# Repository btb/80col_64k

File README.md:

# 80col_64k

Clone of the Extended 80-Column Text Card for Apple IIe

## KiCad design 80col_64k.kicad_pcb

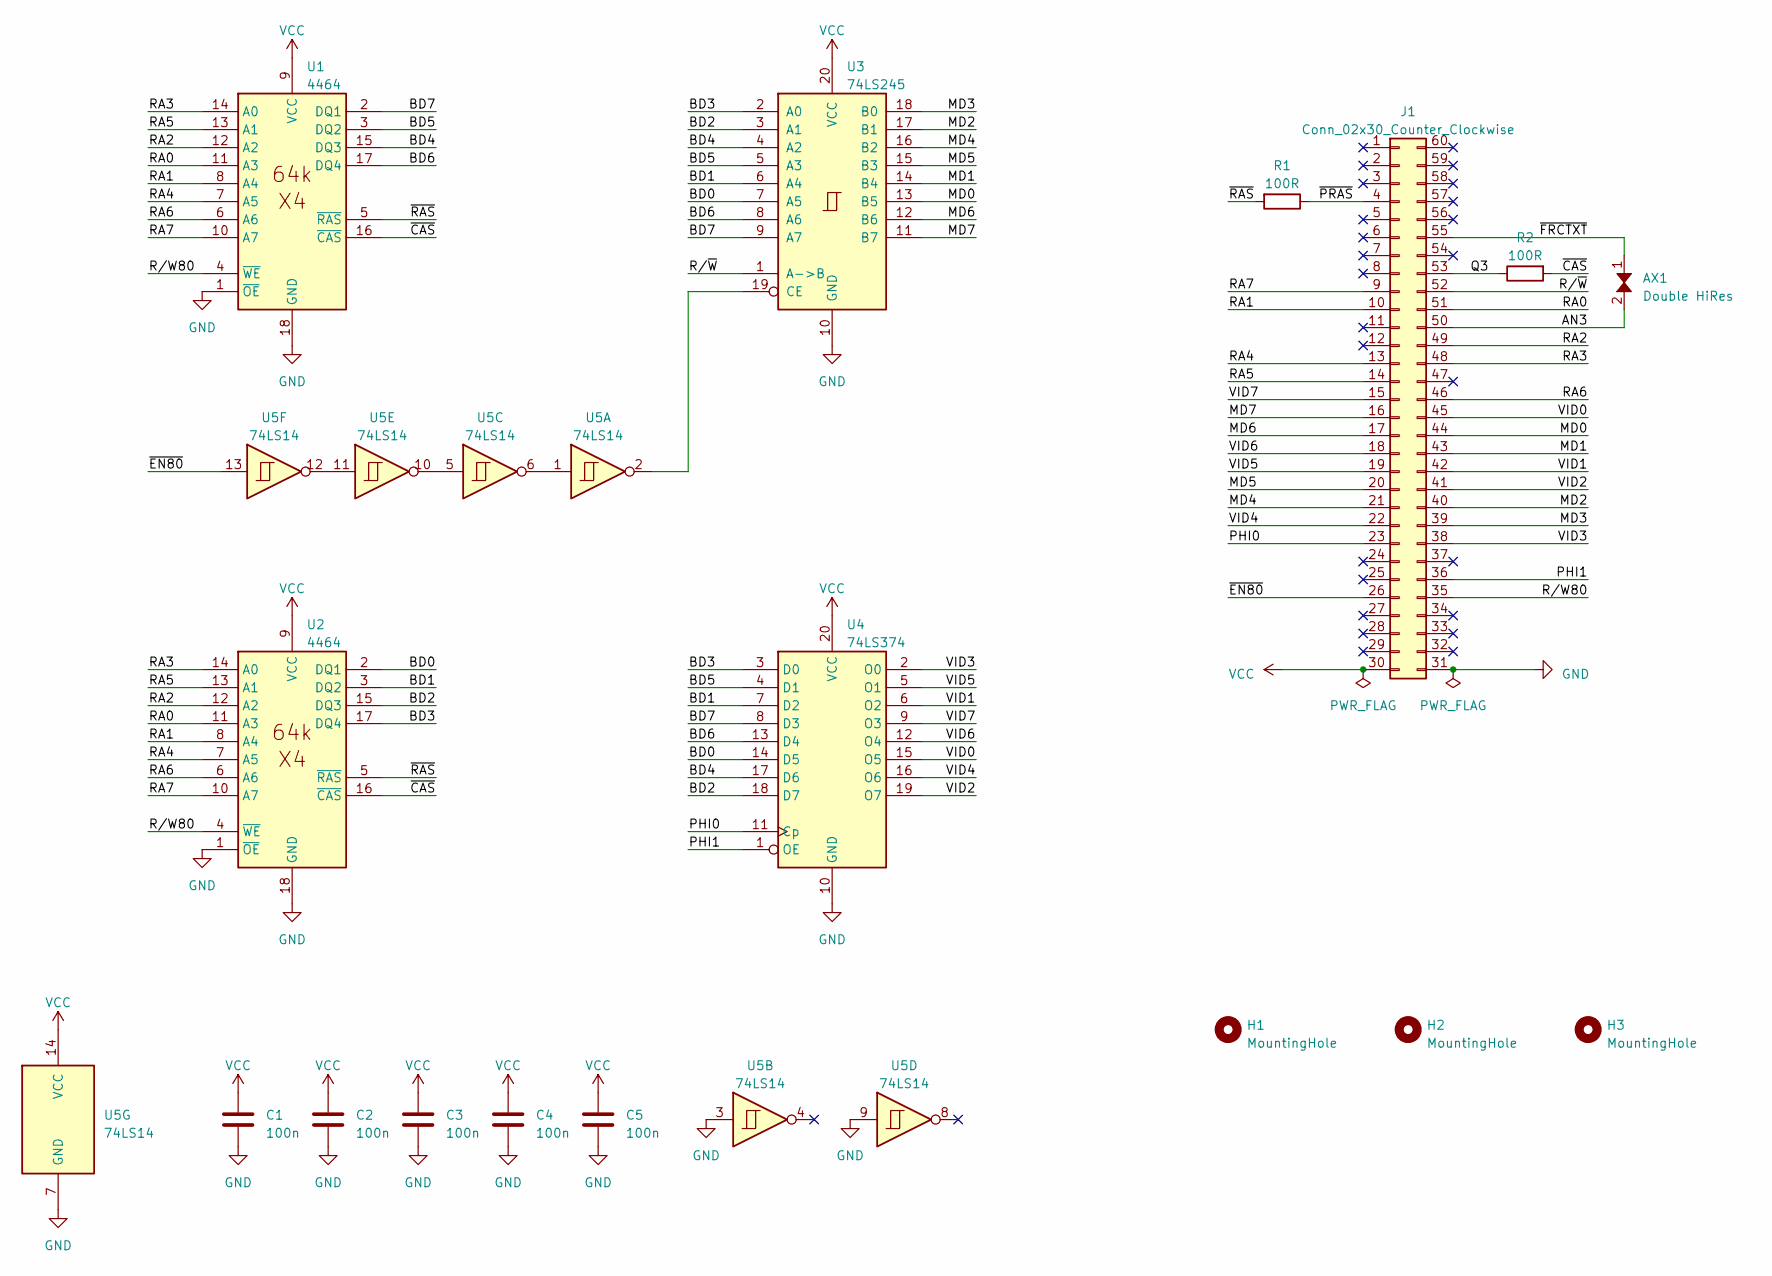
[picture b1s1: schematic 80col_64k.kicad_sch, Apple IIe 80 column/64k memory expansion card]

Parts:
AX1: Double HiRes; SolderJumper-2_Bridged_Bowtie3.81x2.54.mm
C1, C2, C3, C4, C5: 100n; C_Axial_L3.8mm_D2.6mm_P10.00mm_Horizontal
H1, H2, H3: MountingHole; MountingHole_3.2mm_M3
J1: Conn_02x30_Counter_Clockwise; Apple IIe Auxiliary Edge Connector
R1, R2: 100R; R_Axial_DIN0207_L6.3mm_D2.5mm_P12.7mm_Horizontal
U1, U2: 4464; DIP-18_W7.62mm
U3: 74LS245; DIP-20_W7.62mm
U4: 74LS374; DIP-20_W7.62mm
U5: 74LS14; DIP-14_W7.62mm

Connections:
/AN3: AX1.2 (B), J1.50
/BD0: U2.2 (DQ1), U3.7 (A5), U4.14 (D5)
/BD1: U2.3 (DQ2), U3.6 (A4), U4.7 (D2)
/BD2: U2.15 (DQ3), U3.3 (A1), U4.18 (D7)
/BD3: U2.17 (DQ4), U3.2 (A0), U4.3 (D0)
/BD4: U1.15 (DQ3), U3.4 (A2), U4.17 (D6)
/BD5: U1.3 (DQ2), U3.5 (A3), U4.4 (D1)
/BD6: U1.17 (DQ4), U3.8 (A6), U4.13 (D4)
/BD7: U1.2 (DQ1), U3.9 (A7), U4.8 (D3)
/MD0: J1.44, U3.13 (B5)
/MD1: J1.43, U3.14 (B4)
/MD2: J1.40, U3.17 (B1)
/MD3: J1.39, U3.18 (B0)
/MD4: J1.21, U3.16 (B2)
/MD5: J1.20, U3.15 (B3)
/MD6: J1.17, U3.12 (B6)
/MD7: J1.16, U3.11 (B7)
/PHI0: J1.23, U4.11 (Cp)
/PHI1: J1.36, U4.1 (OE)
/Q3: J1.53, R2.1
/RA0: J1.51, U1.11 (A3), U2.11 (A3)
/RA1: J1.10, U1.8 (A4), U2.8 (A4)
/RA2: J1.49, U1.12 (A2), U2.12 (A2)
/RA3: J1.48, U1.14 (A0), U2.14 (A0)
/RA4: J1.13, U1.7 (A5), U2.7 (A5)
/RA5: J1.14, U1.13 (A1), U2.13 (A1)
/RA6: J1.46, U1.6 (A6), U2.6 (A6)
/RA7: J1.9, U1.10 (A7), U2.10 (A7)
/R/W80: J1.35, U1.4 (~WE), U2.4 (~WE)
/R/~W: J1.52, U3.1 (A->B)
/VID0: J1.45, U4.15 (O5)
/VID1: J1.42, U4.6 (O2)
/VID2: J1.41, U4.19 (O7)
/VID3: J1.38, U4.2 (O0)
/VID4: J1.22, U4.16 (O6)
/VID5: J1.19, U4.5 (O1)
/VID6: J1.18, U4.12 (O4)
/VID7: J1.15, U4.9 (O3)
/~CAS: R2.2, U1.16 (~CAS), U2.16 (~CAS)
/~EN80: J1.26, U5.13
/~FRCTXT: AX1.1 (A), J1.55
/~PRAS: J1.4, R1.1
/~RAS: R1.2, U1.5 (~RAS), U2.5 (~RAS)
GND: C1.2, C2.2, C3.2, C4.2, C5.2, J1.31, U1.1 (~OE), U1.18 (GND), U2.1 (~OE), U2.18 (GND), U3.10 (GND), U4.10 (GND), U5.3, U5.7 (GND), U5.9
unnamed: U3.19 (CE), U5.2
unnamed: U5.1, U5.6
unnamed: U5.5, U5.10
unnamed: U5.11, U5.12
VCC: C1.1, C2.1, C3.1, C4.1, C5.1, J1.30, U1.9 (VCC), U2.9 (VCC), U3.20 (VCC), U4.20 (VCC), U5.14 (VCC)

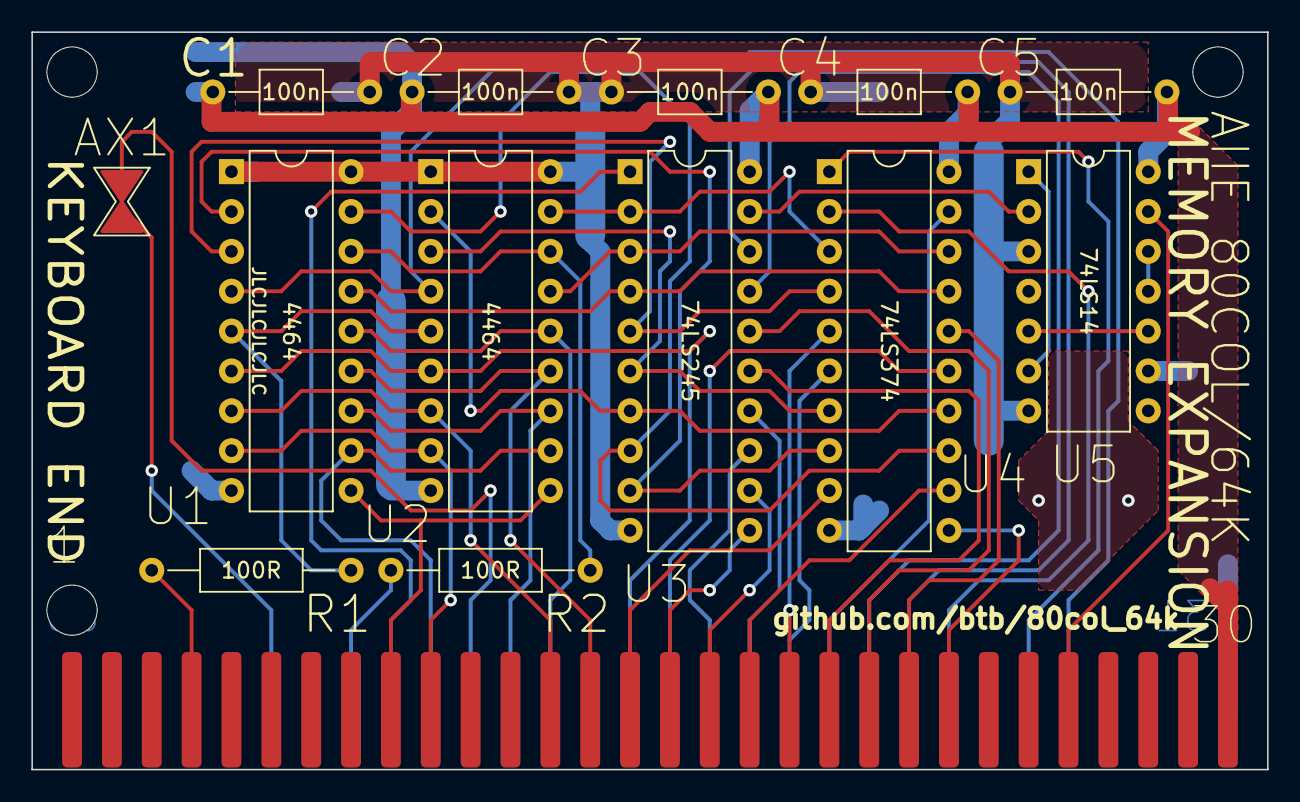
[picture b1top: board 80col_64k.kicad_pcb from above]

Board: 2 copper layers, 78.7 x 47.0 mm, 17 parts (0 on the bottom side), 49 nets.

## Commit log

2023-04-22 add kicad files
2024-02-17 add title block info
2024-02-17 add generated files
